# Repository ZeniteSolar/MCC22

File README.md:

# MCC22

## Build
```bash
cd firmware
make -j16 -f STM32Make.make
```

MPPT Battery charger

| Input Voltage     | 0 ~ 30 V  |
| ----------------: | :-------- |
|   Output Voltage  | 21 ~ 60V  |
| Output Power      | 300 W     |
| Efficiency        | > 90%     |

## 3D Model

## Soldered board

# Testing Guide for the MCC22 Board

Follow the steps below, if any value differs from the expected, abort the test. Power off and on after each step. Always limit the power source to 18V at 100mA. Use this [link](https://htmlpreview.github.io/?https://github.com/ZeniteSolar/MCC22/blob/main/hardware/main/bom/ibom.html) to find components on the board.

## Steps

1. Without any jumpers, connect the CAN with 18V, consumption should be approximately 1mA. On the power pin header (J601) there should be 5V and 3.3V at their respective pins.
2. Connect the STM 3.3V Enable jumper (JP101), consumption should be approximately 1mA.
3. Connect the STM32 Supply Enable jumper (JP201), consumption should be approximately 5mA. There should be 3.3V between the pins of capacitors C208 and C210.
4. Connect the STM 5V Enable jumper (JP103), consumption should be approximately 5mA. There should be 3V across the pins of capacitor C204.
5. Connect the Analog_Ref jumper (JP203) between the central pin and 3V_ref, consumption should be approximately 30mA. There should be 3V across the pins of capacitor C211.
6. Flash the STM32 (power should be on). When power is cycled, all LEDs should light up in sequence, excluding the Bat OverV LED. There should be a PWM signal on pin 1 of the PWM Enable jumper (JP106).
7. Connect the Enable_Analog jumper (JP102), the consumption should be approximately 5mA.
8. Connect a serial-USB converter and send the command `WRTE:SYST:PING?` to verify if UART is functioning, the response should be `PONG`.
9. Send the command `READ:MEAS:ALLM?`. After activating this flag, the board will continuously send the measurements it takes.
10. Connect a 10 Ohm resistor at the controller's output.
11. Send the command `WRTE:CTRL:ALGO:FIXD:0000.0000` to deactivate the PWM.
12. Connect the Disable_Vpanel jumper (JP301), the consumption should remain close to 5mA.
13. Connect the Disable_Vbat jumper (JP302), the consumption should remain close to 5mA.
14. Connect the Disable_Ibat jumper (JP304), the consumption should remain close to 5mA.
15. Connect the Disable_Ipanel jumper (JP303), the consumption should remain close to 5mA.
16. Connect a voltage source at P+ and P- with zero voltage and current at 10mA, increase the voltage to 30V and the VPan value on UART should follow the source voltage.
17. Connect a voltage source at B+ and B- with zero voltage and current at 10mA, increase the voltage to 60V and the Vbat value on UART should follow the source voltage.
18. Connect the Enable_Driver jumper (JP104) and consumption should be approximately 10mA. There should be 15V between pins 3 and 4 of the driver source (PS501).
19. Connect the Enable_Driver_5V jumper (JP502), Enable_Driver jumper (JP501), and Enable_PWM jumper (JP106), and the consumption should be approximately 12mA.
20. Send the command `WRTE:CTRL:ALGO:FIXD:0000.6000` to fix the PWM at 60%. Attach the oscilloscope's GND to test point S (TP404) **Other channels should have their GND disconnected!** and channel 1 to test point G0 (TP401). There should appear a square signal with a 60% duty cycle, same for G1 (TP402).
21. Connect a 10 Ohm load at the controller's output. Send the command `WRTE:CTRL:ALGO:FIXD:0000.6000`, connect a voltage source at P+ and P- with zero voltage and current at 1A, increase the voltage until the source limits and the Ipan value on UART should follow the source current.

Note: If any of the conditions are not met, there might be a potential issue with the board.

## Tests

All tests are in [this](./tests/tests.md) separated document.

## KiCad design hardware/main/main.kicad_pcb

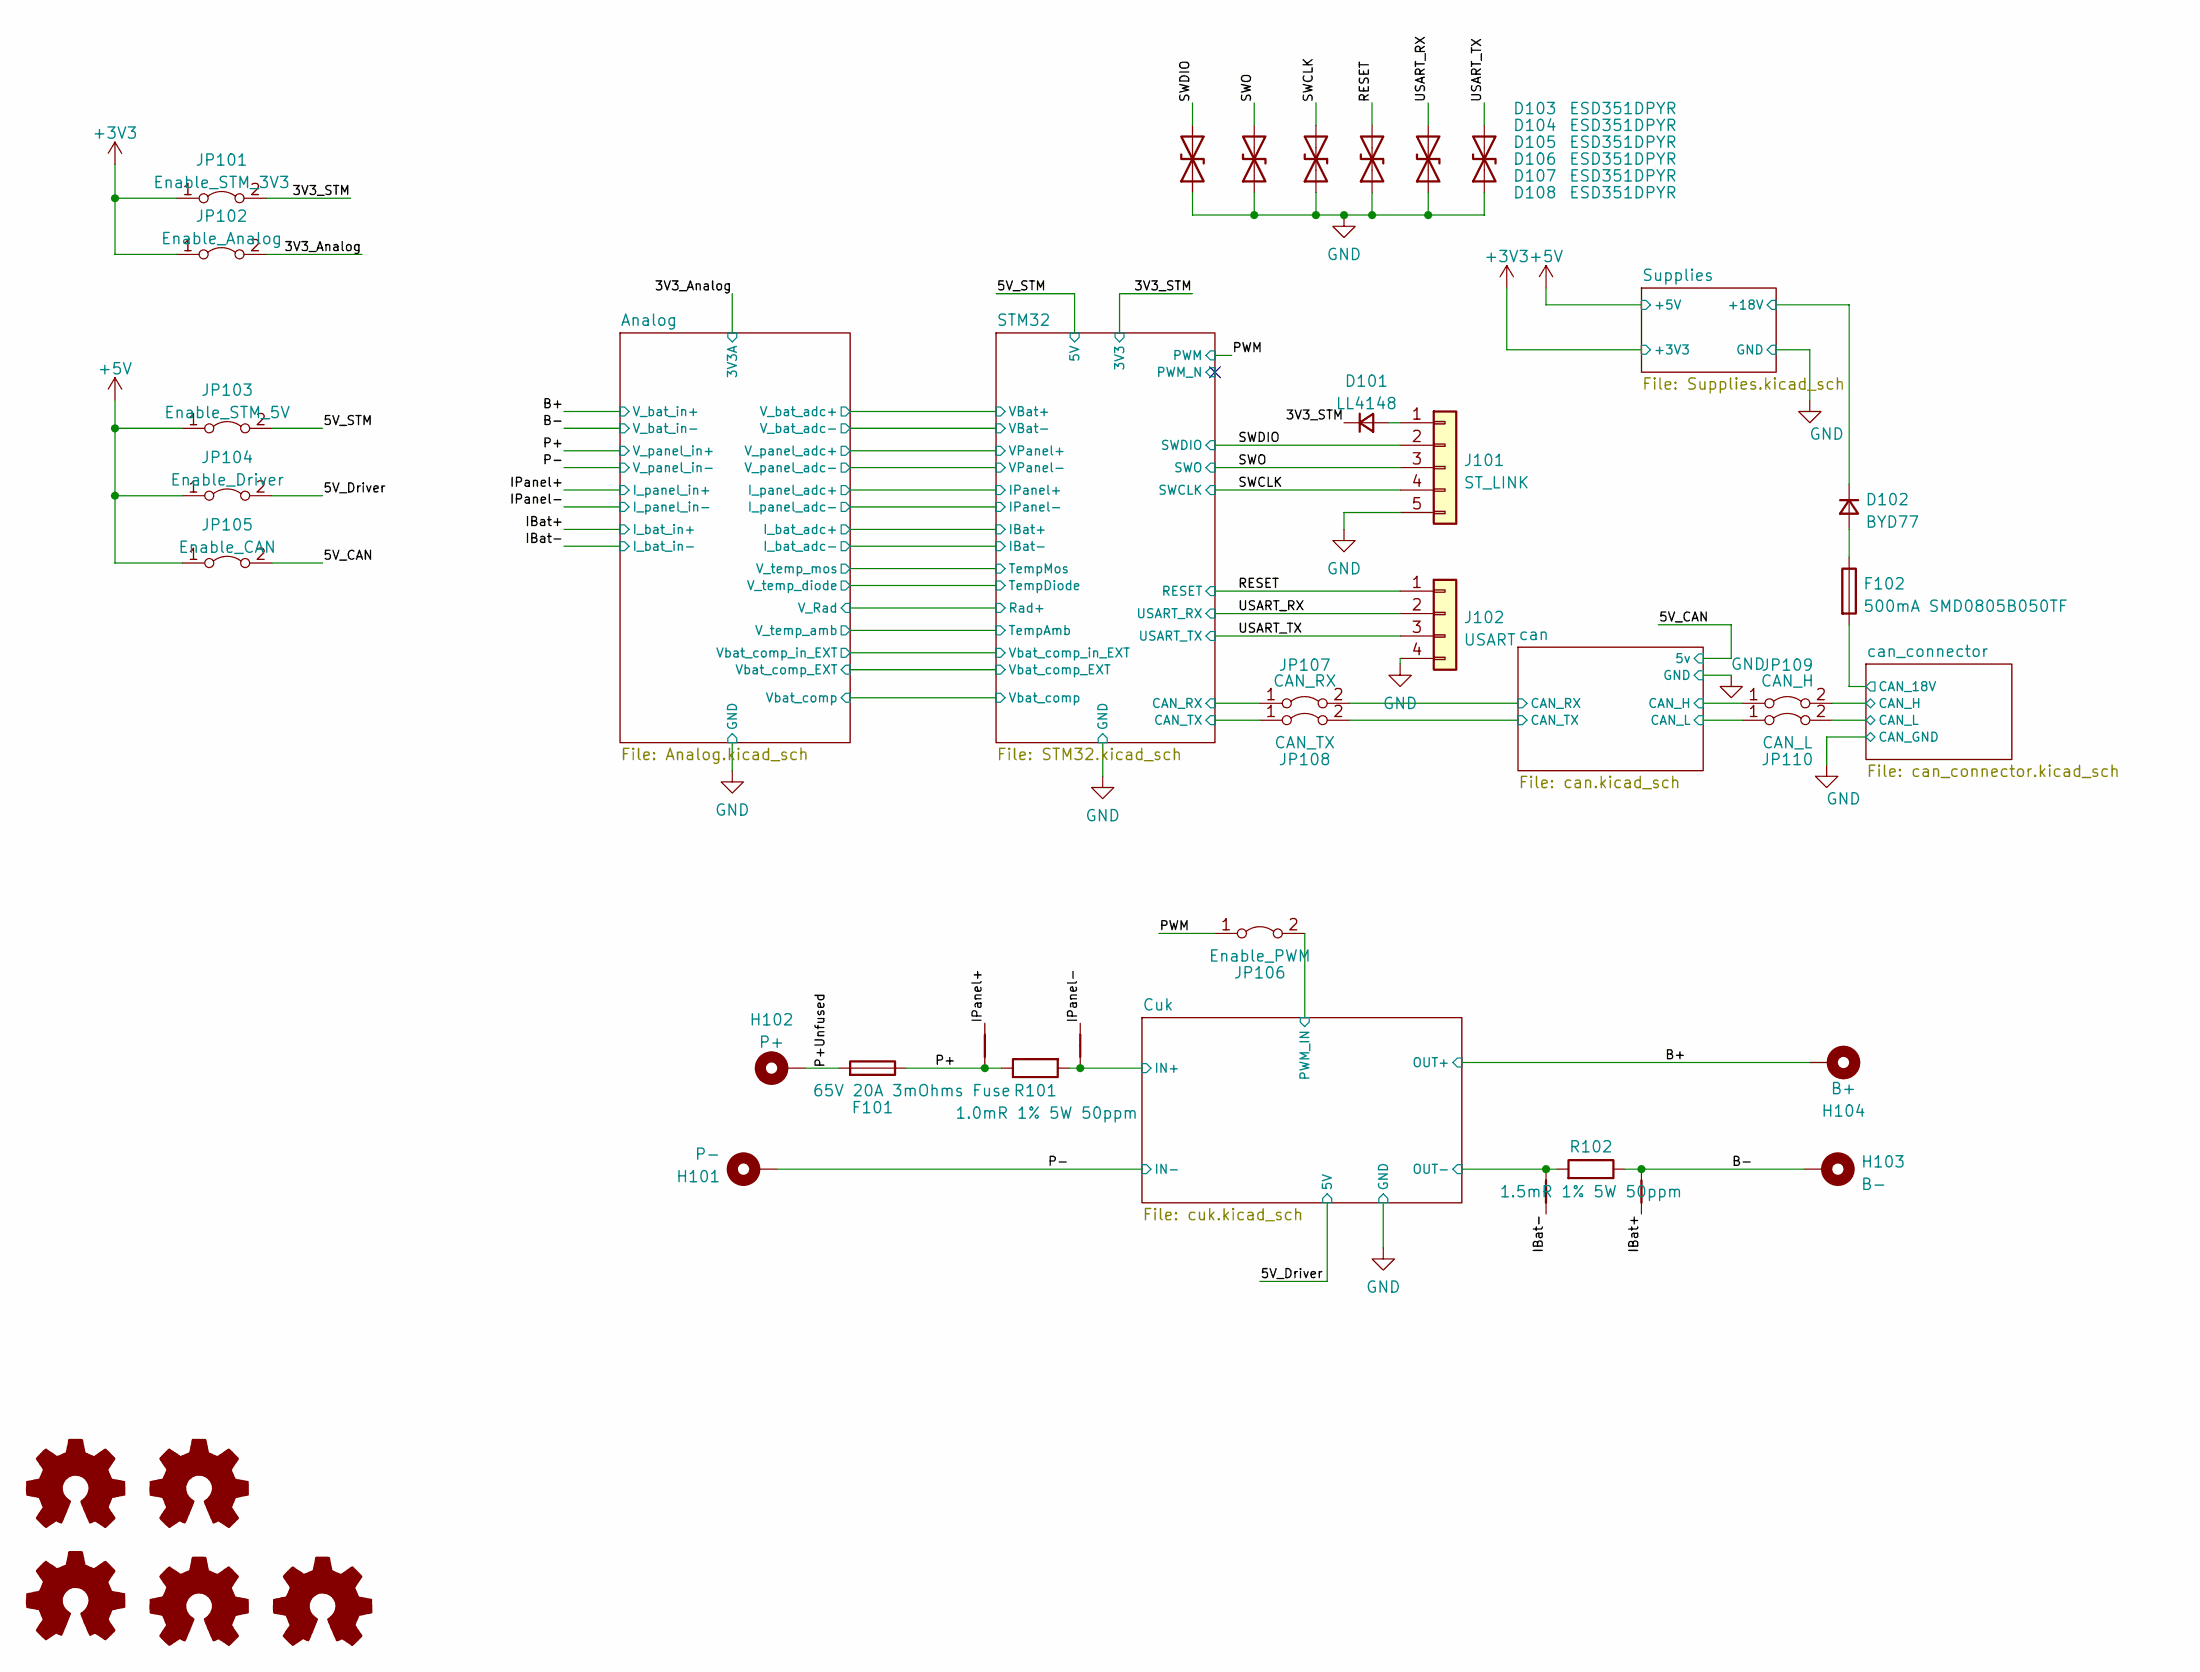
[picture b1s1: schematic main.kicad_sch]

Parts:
D101: LL4148; D_MiniMELF_Handsoldering
D102: BYD77; D_MiniMELF_Handsoldering
D103, D104, D105, D106, D107, D108: ESD351DPYR; D_0402_1005Metric_Pad0.77x0.64mm_HandSolder
F101: 65V 20A 3mOhms Fuse; S6125-F
F102: 500mA SMD0805B050TF; Fuse_0805_2012Metric_Pad1.15x1.40mm_HandSolder
H101: P-; MountingHole_13mmx13mm_Rectangular
H102: P+; MountingHole_13mmx13mm_Rectangular
H103: B-; MountingHole_13mmx13mm_Rectangular
H104: B+; MountingHole_13mmx13mm_Rectangular
J101: ST_LINK; PinSocket_1x05_P2.54mm_Horizontal_SMD
J102: USART; PinSocket_1x04_P2.54mm_Horizontal_SMD
JP101: Enable_STM_3V3; SolderJumper-2_P0.5mm_Open_TrianglePad0.8x0.5mm
JP102: Enable_Analog; SolderJumper-2_P0.5mm_Open_TrianglePad0.8x0.5mm
JP103: Enable_STM_5V; SolderJumper-2_P0.5mm_Open_TrianglePad0.8x0.5mm
JP104: Enable_Driver; SolderJumper-2_P0.5mm_Open_TrianglePad0.8x0.5mm
JP105: Enable_CAN; SolderJumper-2_P0.5mm_Open_TrianglePad0.8x0.5mm
JP106: Enable_PWM; SolderJumper-2_P0.5mm_Open_TrianglePad0.8x0.5mm
JP107: CAN_RX; SolderJumper-2_P0.5mm_Open_TrianglePad0.8x0.5mm
JP108: CAN_TX; SolderJumper-2_P0.5mm_Open_TrianglePad0.8x0.5mm
JP109: CAN_H; SolderJumper-2_P0.5mm_Open_TrianglePad0.8x0.5mm
JP110: CAN_L; SolderJumper-2_P0.5mm_Open_TrianglePad0.8x0.5mm
LOGO101: Logo_Open_Hardware_Small; symbol_logoZenite
LOGO102: Logo_Open_Hardware_Small; synbol_logoifsc
LOGO103: Logo_Open_Hardware_Small; OSHW-Logo_5.7x6mm_SilkScreen
LOGO104: Logo_Open_Hardware_Small; symbol_logoZenite_small
LOGO105: Logo_Open_Hardware_Small; synbol_logoifsc_small
NT101, NT102, NT104: NetTie_2; NetTie-2_SMD_Pad0.3mm
NT103: Resistor_SMD:R_0201_0603Metric; NetTie-2_SMD_Pad0.3mm
R101: 1.0mR 1% 5W 50ppm; R_2512_6332Metric_Pad1.40x3.35mm_HandSolder
R102: 1.5mR 1% 5W 50ppm; R_2512_6332Metric_Pad1.40x3.35mm_HandSolder

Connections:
+3V3: JP101.1 (A), JP102.1 (A); also elsewhere on the board
+5V: JP103.1 (A), JP104.1 (A), JP105.1 (A); also elsewhere on the board
/3V3_Analog: JP102.2 (B); also elsewhere on the board
/3V3_STM: D101.1 (K), JP101.2 (B); also elsewhere on the board
/5V_CAN: JP105.2 (B); also elsewhere on the board
/5V_Driver: JP104.2 (B); also elsewhere on the board
/5V_STM: JP103.2 (B); also elsewhere on the board
/B+: H104.1; also elsewhere on the board
/B-: H103.1, NT104.2, R102.1; also elsewhere on the board
/Cuk/A: NT102.2, NT103.2, R101.2, R102.2; also elsewhere on the board
/Cuk/PWM_IN: JP106.2 (B); also elsewhere on the board
/IBat+: NT104.1; also elsewhere on the board
/IBat-: NT103.1; also elsewhere on the board
/IPanel+: NT101.1; also elsewhere on the board
/IPanel-: NT102.1; also elsewhere on the board
/P+: F101.1, NT101.2, R101.1; also elsewhere on the board
/P+Unfused: F101.2, H102.1
/P-: H101.1; also elsewhere on the board
/PWM: JP106.1 (A); also elsewhere on the board
/RESET: D106.2 (A2), J102.1; also elsewhere on the board
/STM32/CAN_RX: JP107.1 (A); also elsewhere on the board
/STM32/CAN_TX: JP108.1 (A); also elsewhere on the board
/SWCLK: D105.2 (A2), J101.4; also elsewhere on the board
/SWDIO: D103.2 (A2), J101.2; also elsewhere on the board
/SWO: D104.2 (A2), J101.3; also elsewhere on the board
/Supplies/+18V: D102.1 (K); also elsewhere on the board
/USART_RX: D107.2 (A2), J102.2; also elsewhere on the board
/USART_TX: D108.2 (A2), J102.3; also elsewhere on the board
/can/CAN_H: JP109.1 (A); also elsewhere on the board
/can/CAN_L: JP110.1 (A); also elsewhere on the board
/can/CAN_RX: JP107.2 (B); also elsewhere on the board
/can/CAN_TX: JP108.2 (B); also elsewhere on the board
/can_connector/CAN_18V: F102.2; also elsewhere on the board
/can_connector/CAN_H: JP109.2 (B); also elsewhere on the board
/can_connector/CAN_L: JP110.2 (B); also elsewhere on the board
GND: D103.1 (A1), D104.1 (A1), D105.1 (A1), D106.1 (A1), D107.1 (A1), D108.1 (A1), J101.5, J102.4; also elsewhere on the board
unnamed: D101.2 (A), J101.1
unnamed: D102.2 (A), F102.1

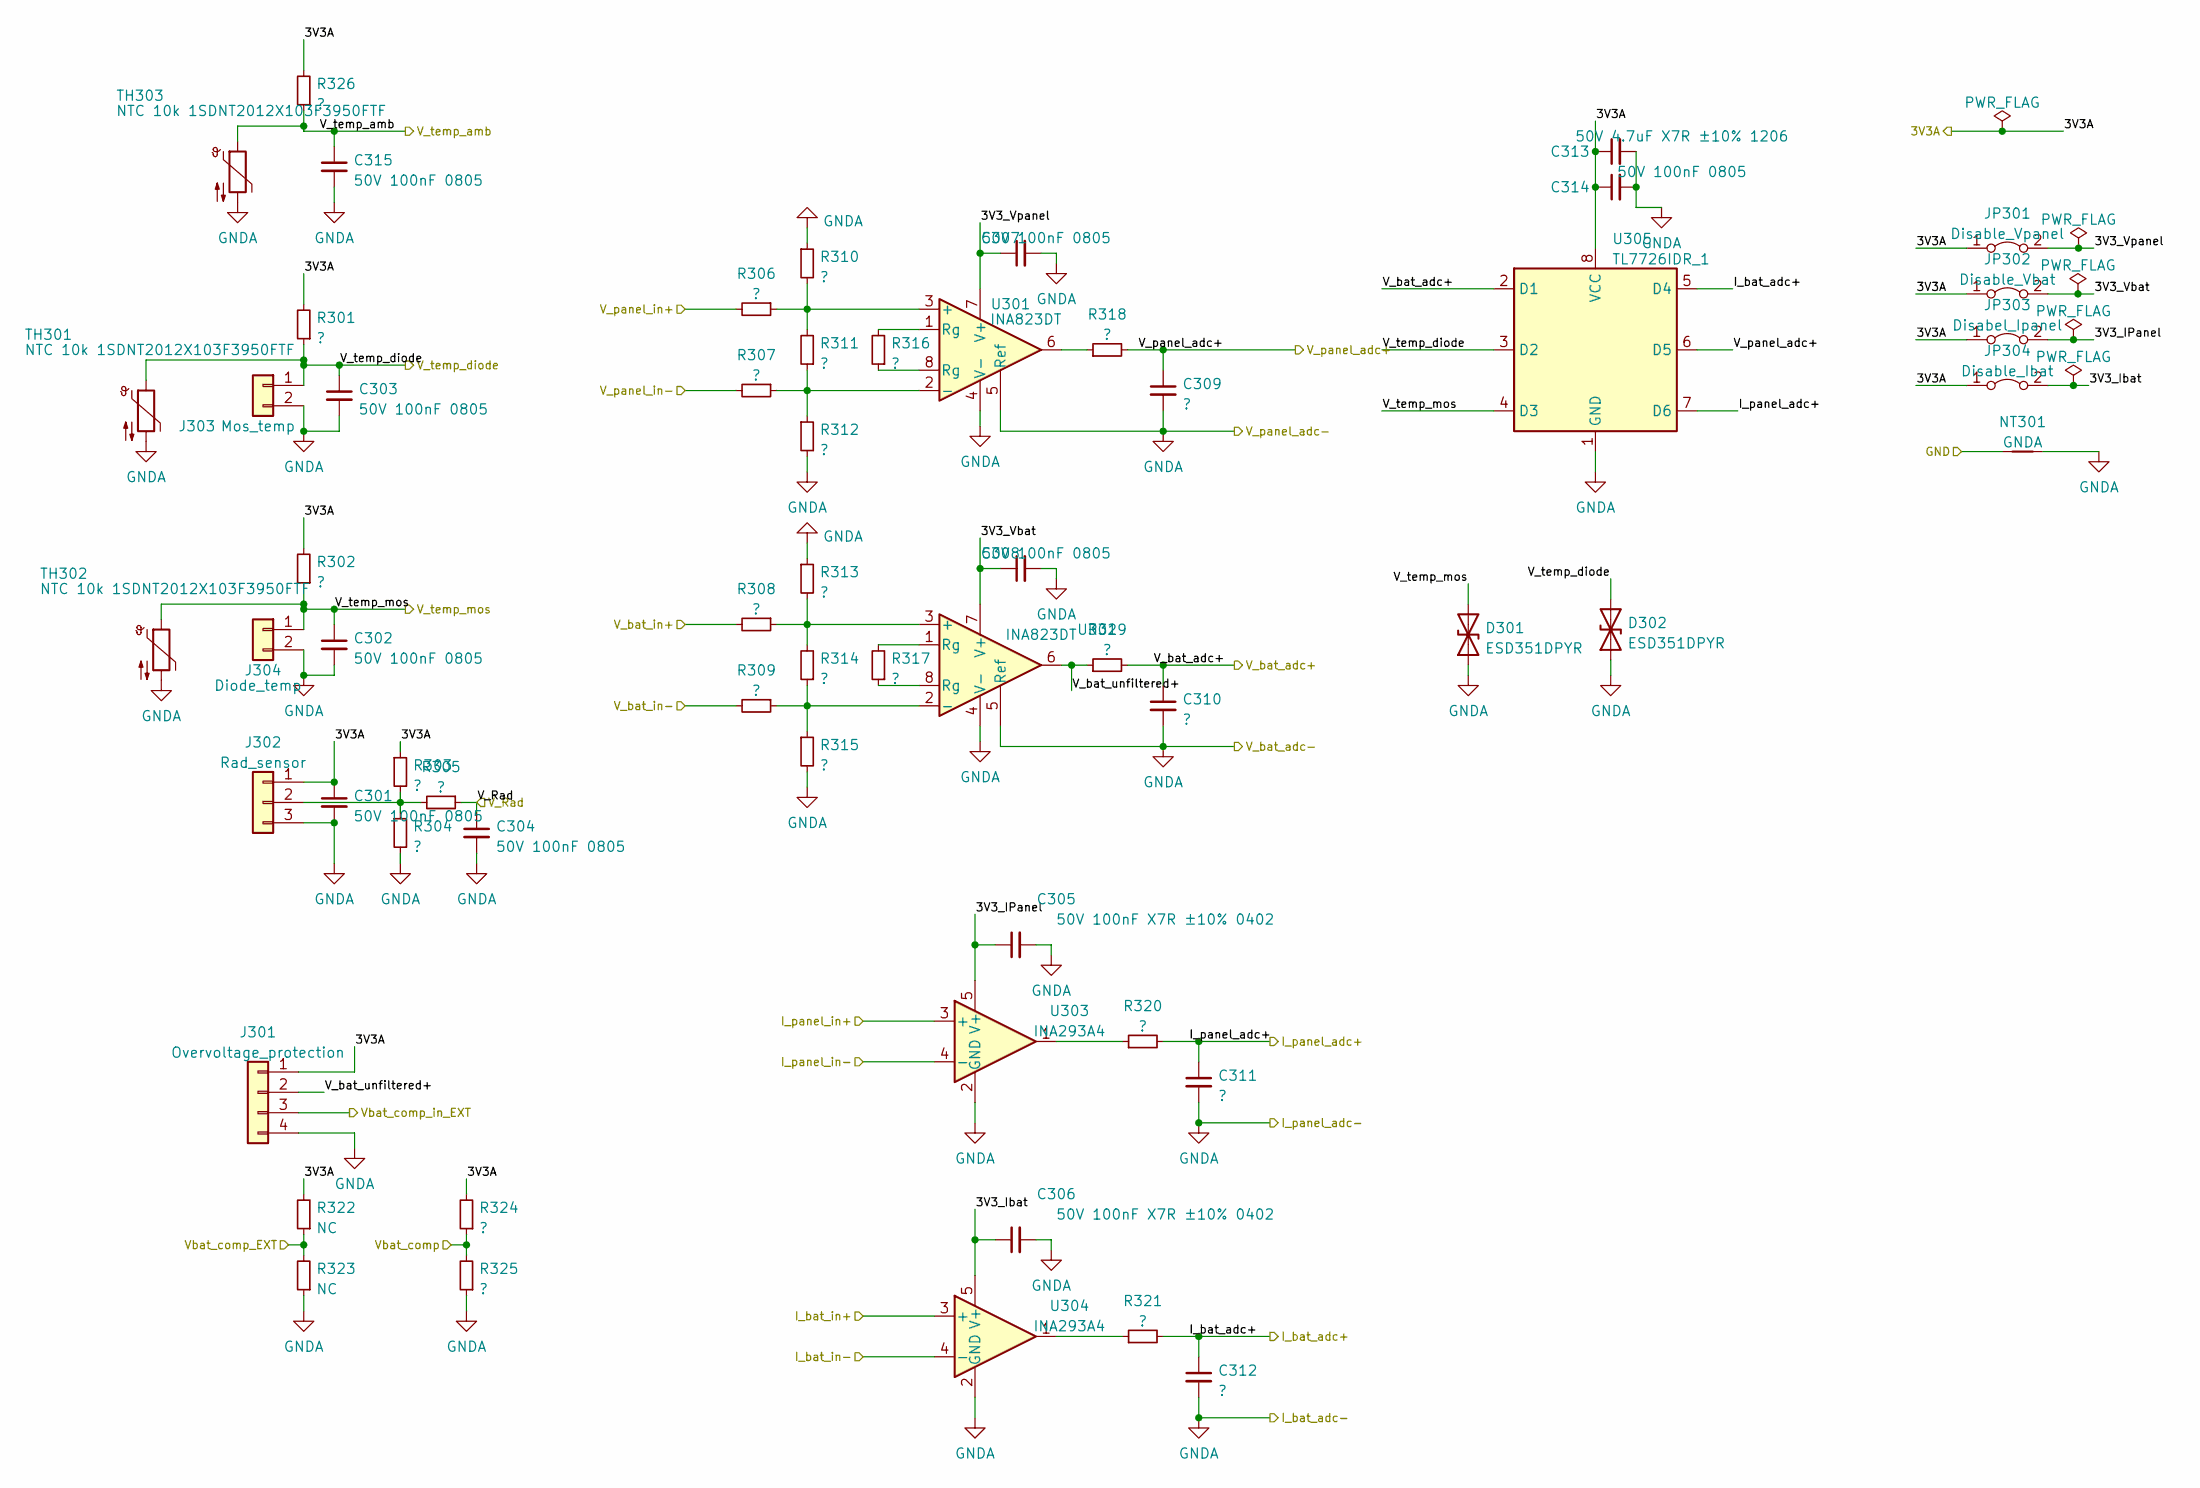
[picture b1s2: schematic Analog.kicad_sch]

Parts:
C301, C302, C303, C304, C307, C308, C314, C315: 50V 100nF 0805; C_0805_2012Metric_Pad1.18x1.45mm_HandSolder
C305, C306: 50V 100nF X7R ±10% 0402; C_0402_1005Metric_Pad0.74x0.62mm_HandSolder
C309, C310, C311, C312: ?; C_0805_2012Metric_Pad1.18x1.45mm_HandSolder
C313: 50V 4.7uF X7R ±10% 1206; C_1206_3216Metric_Pad1.33x1.80mm_HandSolder
D301, D302: ESD351DPYR; D_0402_1005Metric_Pad0.77x0.64mm_HandSolder
J301: Overvoltage_protection; PinHeader_1x04_P2.54mm_Vertical
J302: Rad_sensor; PinHeader_1x03_P2.54mm_Vertical
J303: Mos_temp; PinHeader_1x02_P2.54mm_Vertical
J304: Diode_temp; PinHeader_1x02_P2.54mm_Vertical
JP301: Disable_Vpanel; SolderJumper-2_P0.5mm_Open_TrianglePad0.8x0.5mm
JP302: Disable_Vbat; SolderJumper-2_P0.5mm_Open_TrianglePad0.8x0.5mm
JP303: Disabel_Ipanel; SolderJumper-2_P0.5mm_Open_TrianglePad0.8x0.5mm
JP304: Disable_Ibat; SolderJumper-2_P0.5mm_Open_TrianglePad0.8x0.5mm
NT301: GNDA; NetTie-2_SMD_Pad0.3mm
R301, R302, R303, R304, R305, R306, R307, R308, R309, R310, R311, R312, R313, R314, R315, R316, R317, R318, R319, R320, R321, R324, R325, R326: ?; R_0805_2012Metric_Pad1.20x1.40mm_HandSolder
R322, R323: NC; R_0805_2012Metric_Pad1.20x1.40mm_HandSolder
TH301, TH302, TH303: NTC 10k 1SDNT2012X103F3950FTF; R_0805_2012Metric_Pad1.20x1.40mm_HandSolder
U301, U302: INA823DT; SOIC-8_3.9x4.9mm_P1.27mm
U303, U304: INA293A4; SOT-23-5_HandSoldering
U305: TL7726IDR_1; SOIC-8_3.9x4.9mm_P1.27mm

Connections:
/3V3_Analog: C301.1, C313.1, C314.1, J301.1, J302.1, JP301.1 (A), JP302.1 (A), JP303.1 (A), JP304.1 (A), R301.2, R302.2, R303.1, R322.2, R324.2, R326.2, U305.8 (VCC); also elsewhere on the board
/Analog/3V3_IPanel: C305.1, JP303.2 (B), U303.5 (V+)
/Analog/3V3_Ibat: C306.1, JP304.2 (B), U304.5 (V+)
/Analog/3V3_Vbat: C308.1, JP302.2 (B), U302.7 (V+)
/Analog/3V3_Vpanel: C307.1, JP301.2 (B), U301.7 (V+)
/Analog/I_bat_adc+: C312.1, R321.2, U305.5 (D4); also elsewhere on the board
/Analog/I_panel_adc+: C311.1, R320.2, U305.7 (D6); also elsewhere on the board
/Analog/V_Rad: C304.1, R305.1; also elsewhere on the board
/Analog/V_bat_adc+: C310.1, R319.2, U305.2 (D1); also elsewhere on the board
/Analog/V_bat_unfiltered+: J301.2, R319.1, U302.6
/Analog/V_panel_adc+: C309.1, R318.2, U305.6 (D5); also elsewhere on the board
/Analog/V_temp_amb: C315.1, R326.1, TH303.1; also elsewhere on the board
/Analog/V_temp_diode: C303.1, D302.2 (A2), J303.1, R301.1, TH301.1, U305.3 (D2); also elsewhere on the board
/Analog/V_temp_mos: C302.1, D301.2 (A2), J304.1, R302.1, TH302.1, U305.4 (D3); also elsewhere on the board
/Analog/Vbat_comp: R324.1, R325.2; also elsewhere on the board
/Analog/Vbat_comp_EXT: R322.1, R323.2; also elsewhere on the board
/Analog/Vbat_comp_in_EXT: J301.3; also elsewhere on the board
/B+: R308.2; also elsewhere on the board
/B-: R309.2; also elsewhere on the board
/IBat+: U304.3 (+); also elsewhere on the board
/IBat-: U304.4 (-); also elsewhere on the board
/IPanel+: U303.3 (+); also elsewhere on the board
/IPanel-: U303.4 (-); also elsewhere on the board
/P+: R306.2; also elsewhere on the board
/P-: R307.2; also elsewhere on the board
GND: NT301.1; also elsewhere on the board
GNDA: C301.2, C302.2, C303.2, C304.2, C305.2, C306.2, C307.2, C308.2, C309.2, C310.2, C311.2, C312.2, C313.2, C314.2, C315.2, D301.1 (A1), D302.1 (A1), J301.4, J302.3, J303.2, J304.2, NT301.2, R304.2, R310.1, R312.2, R313.1, R315.2, R323.1, R325.1, TH301.2, TH302.2, TH303.2, U301.4 (V-), U301.5 (Ref), U302.4 (V-), U302.5 (Ref), U303.2 (GND), U304.2 (GND), U305.1 (GND); also elsewhere on the board
unnamed: J302.2, R303.2, R304.1, R305.2
unnamed: R306.1, R310.2, R311.2, U301.3 (+)
unnamed: R307.1, R311.1, R312.1, U301.2 (-)
unnamed: R308.1, R313.2, R314.2, U302.3 (+)
unnamed: R309.1, R314.1, R315.1, U302.2 (-)
unnamed: R316.1, U301.8 (Rg)
unnamed: R316.2, U301.1 (Rg)
unnamed: R317.1, U302.8 (Rg)
unnamed: R317.2, U302.1 (Rg)
unnamed: R318.1, U301.6
unnamed: R320.1, U303.1
unnamed: R321.1, U304.1

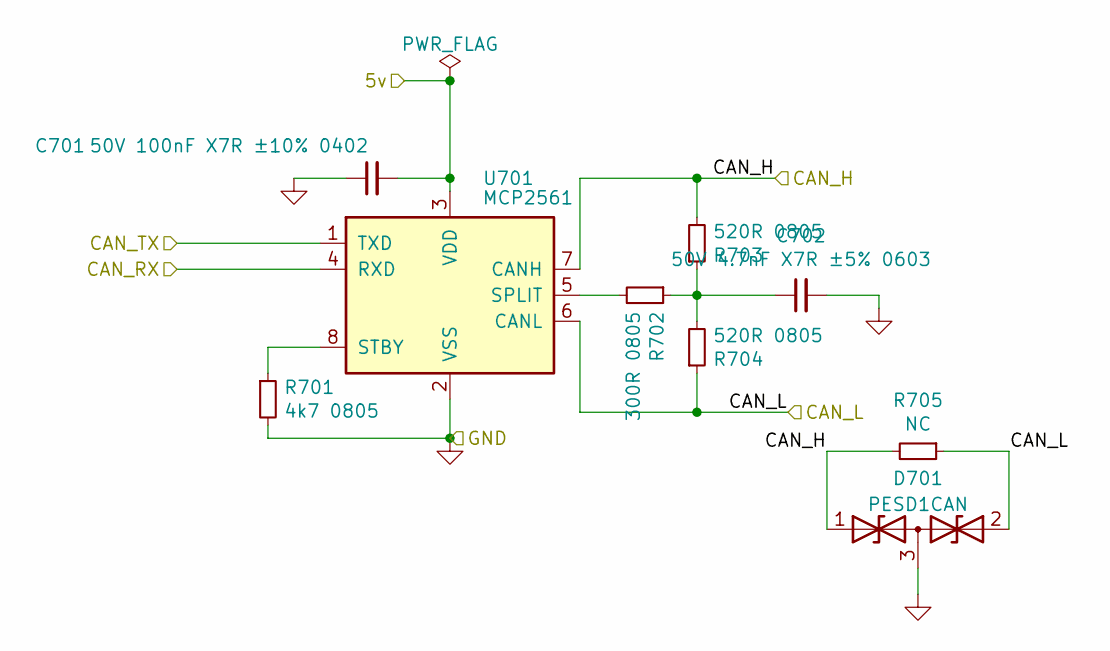
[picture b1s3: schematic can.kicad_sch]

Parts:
C701: 50V 100nF X7R ±10% 0402; C_0402_1005Metric_Pad0.74x0.62mm_HandSolder
C702: 50V 4.7nF X7R ±5% 0603; C_0603_1608Metric_Pad1.08x0.95mm_HandSolder
D701: PESD1CAN; SOT-23_Handsoldering
R701: 4k7 0805; R_0805_2012Metric_Pad1.20x1.40mm_HandSolder
R702: 300R 0805; R_0805_2012Metric_Pad1.20x1.40mm_HandSolder
R703, R704: 520R 0805; R_0805_2012Metric_Pad1.20x1.40mm_HandSolder
R705: NC; R_0805_2012Metric_Pad1.20x1.40mm_HandSolder
U701: MCP2561; SOIC-8_3.9x4.9mm_P1.27mm

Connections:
/5V_CAN: C701.2, U701.3 (VDD); also elsewhere on the board
/can/CAN_H: D701.1 (A1), R703.2, R705.2, U701.7 (CANH); also elsewhere on the board
/can/CAN_L: D701.2 (A2), R704.1, R705.1, U701.6 (CANL); also elsewhere on the board
/can/CAN_RX: U701.4 (RXD); also elsewhere on the board
/can/CAN_TX: U701.1 (TXD); also elsewhere on the board
GND: C701.1, C702.2, D701.3 (common), R701.2, U701.2 (VSS); also elsewhere on the board
unnamed: C702.1, R702.1, R703.1, R704.2
unnamed: R701.1, U701.8 (STBY)
unnamed: R702.2, U701.5 (SPLIT)

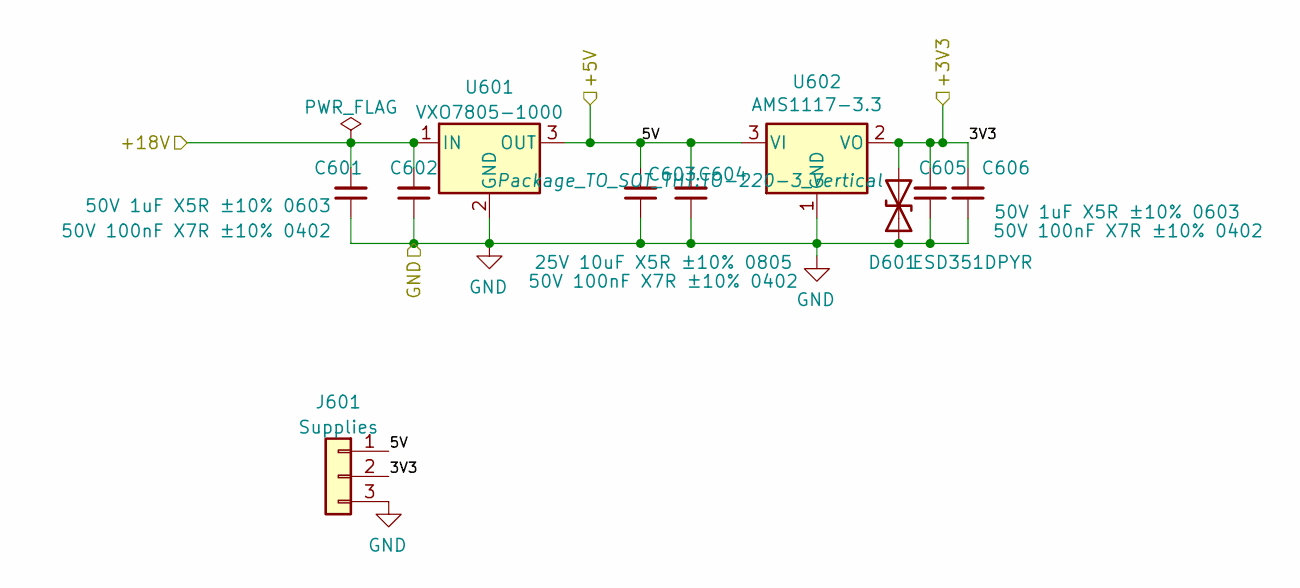
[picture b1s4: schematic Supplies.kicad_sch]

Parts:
C601, C606: 50V 1uF X5R ±10% 0603; C_1206_3216Metric_Pad1.33x1.80mm_HandSolder
C602, C604, C605: 50V 100nF X7R ±10% 0402; C_0603_1608Metric_Pad1.08x0.95mm_HandSolder
C603: 25V 10uF X5R ±10% 0805; C_1206_3216Metric_Pad1.33x1.80mm_HandSolder
D601: ESD351DPYR; D_0402_1005Metric_Pad0.77x0.64mm_HandSolder
J601: Supplies; PinHeader_1x03_P2.54mm_Vertical
U601: VXO7805-1000; TO-220-3_Vertical
U602: AMS1117-3.3; SOT-223-3_TabPin2

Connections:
+3V3: C605.2, C606.2, D601.2 (A2), J601.2, U602.2 (VO); also elsewhere on the board
+5V: C603.2, C604.2, J601.1, U601.3 (OUT), U602.3 (VI); also elsewhere on the board
/Supplies/+18V: C601.2, C602.2, U601.1 (IN); also elsewhere on the board
GND: C601.1, C602.1, C603.1, C604.1, C605.1, C606.1, D601.1 (A1), J601.3, U601.2 (GND), U602.1 (GND); also elsewhere on the board

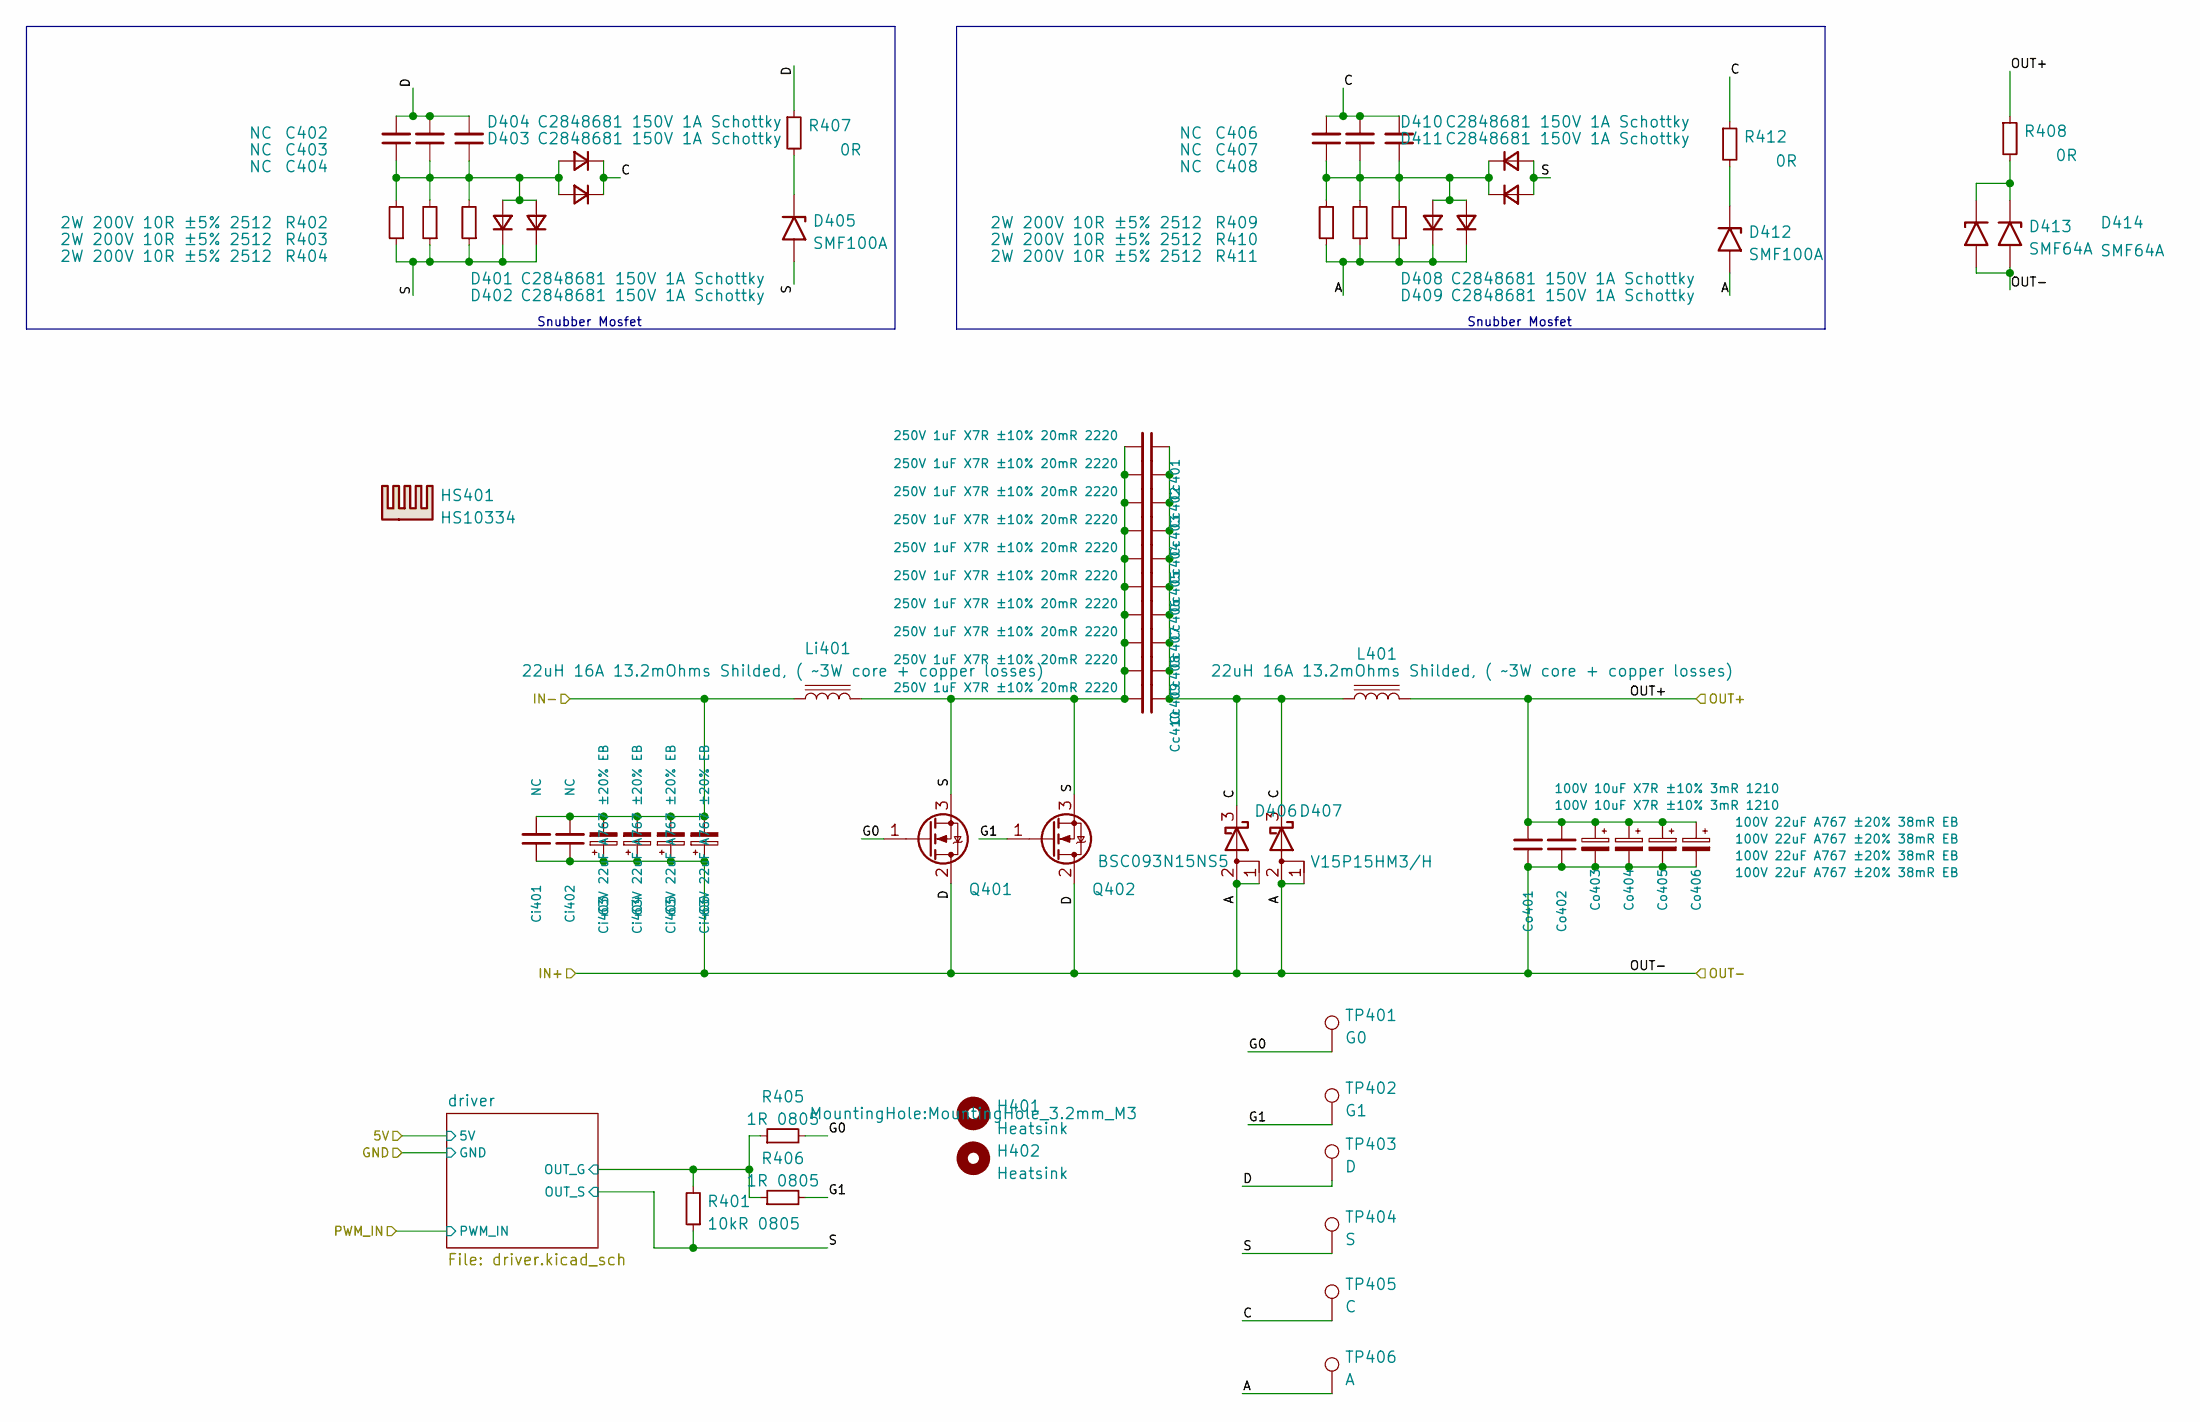
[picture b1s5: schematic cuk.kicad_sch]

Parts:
C402, C403, C404, C406, C407, C408: NC; C_1206_3216Metric_Pad1.33x1.80mm_HandSolder
Cc401, Cc402, Cc403, Cc404, Cc405, Cc406, Cc407, Cc408, Cc409, Cc410: 250V 1uF X7R ±10% 20mR 2220; C_2220_5650Metric
Ci401, Ci402: NC; C_1210_3225Metric
Ci403, Ci404, Ci405, Ci406: 63V 22uF A767 ±20% EB; CP_Elec_8x10
Co401, Co402: 100V 10uF X7R ±10% 3mR 1210; C_1210_3225Metric
Co403, Co404, Co405, Co406: 100V 22uF A767 ±20% 38mR EB; CP_Elec_10x12.5
D401, D402, D403, D404, D408, D409, D410, D411: C2848681 150V 1A Schottky; D_SMA
D405, D412: SMF100A; D_SOD-123F
D406, D407: V15P15HM3/H; TO-277A
D413, D414: SMF64A; D_SOD-123F
H401, H402: Heatsink; MountingHole_3.2mm_M3
HS401: HS10334; HS10334 60mmx17mm
L401: 22uH 16A 13.2mOhms Shilded, ( ~3W core + copper l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; L_Pulse_PM227
Li401: 22uH 16A 13.2mOhms Shilded, ( ~3W core + copper l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; L_Pulse_PM227
Q401, Q402: BSC093N15NS5; TDSON-8-3
R401: 10kR 0805; R_0805_2012Metric_Pad1.20x1.40mm_HandSolder
R402, R403, R404, R409, R410, R411: 2W 200V 10R ±5% 2512; R_2512_6332Metric_Pad1.40x3.35mm_HandSolder
R405, R406: 1R 0805; R_0805_2012Metric_Pad1.20x1.40mm_HandSolder
R407, R408, R412: 0R; R_0805_2012Metric_Pad1.20x1.40mm_HandSolder
TP401: G0; TestPoint_Pad_1.5x1.5mm
TP402: G1; TestPoint_Pad_1.5x1.5mm
TP403: D; TestPoint_Pad_1.5x1.5mm
TP404: S; TestPoint_Pad_1.5x1.5mm
TP405: C; TestPoint_Pad_1.5x1.5mm
TP406: A; TestPoint_Pad_1.5x1.5mm

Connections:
/B+: Co401.2, Co402.2, Co403.1, Co404.1, Co405.1, Co406.1, L401.2, R408.1; also elsewhere on the board
/Cuk/A: C402.2, C403.2, C404.2, Ci401.1, Ci402.1, Ci403.1, Ci404.1, Ci405.1, Ci406.1, Co401.1, Co402.1, Co403.2, Co404.2, Co405.2, Co406.2, D406.1 (A), D406.2 (A), D407.1 (A), D407.2 (A), D408.1 (K), D409.1 (K), D412.2 (A2), D413.2 (A2), D414.2 (A2), Q401.2 (D), Q402.2 (D), R407.1, R409.1, R410.1, R411.1, TP403.1, TP406.1; also elsewhere on the board
/Cuk/C: C406.2, C407.2, C408.2, Cc401.1, Cc402.1, Cc403.1, Cc404.1, Cc405.1, Cc406.1, Cc407.1, Cc408.1, Cc409.1, Cc410.1, D403.1 (K), D404.1 (K), D406.3 (K), D407.3 (K), L401.1, R412.1, TP405.1
/Cuk/G0: Q401.1 (G), R405.2, TP401.1
/Cuk/G1: Q402.1 (G), R406.2, TP402.1
/Cuk/S: Cc401.2, Cc402.2, Cc403.2, Cc404.2, Cc405.2, Cc406.2, Cc407.2, Cc408.2, Cc409.2, Cc410.2, D401.1 (K), D402.1 (K), D405.2 (A2), D410.2 (A), D411.2 (A), Li401.1, Q401.3 (S), Q402.3 (S), R401.1, R402.1, R403.1, R404.1, TP404.1; also elsewhere on the board
/Cuk/driver/OUT_G: R401.2, R405.1, R406.1; also elsewhere on the board
/P-: Ci401.2, Ci402.2, Ci403.2, Ci404.2, Ci405.2, Ci406.2, Li401.2; also elsewhere on the board
unnamed: C402.1, C403.1, C404.1, D401.2 (A), D402.2 (A), D403.2 (A), D404.2 (A), R402.2, R403.2, R404.2
unnamed: C406.1, C407.1, C408.1, D408.2 (A), D409.2 (A), D410.1 (K), D411.1 (K), R409.2, R410.2, R411.2
unnamed: D405.1 (A1), R407.2
unnamed: D412.1 (A1), R412.2
unnamed: D413.1 (A1), D414.1 (A1), R408.2

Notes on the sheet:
Snubber Mosfet

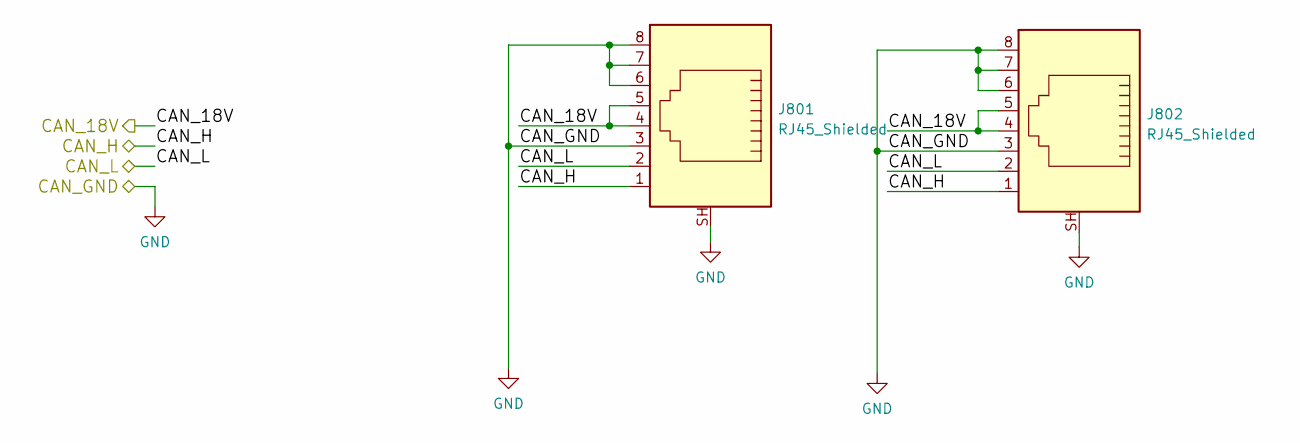
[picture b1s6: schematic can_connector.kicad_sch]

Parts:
J801, J802: RJ45_Shielded; RJ45_YH59_01

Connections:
/can_connector/CAN_18V: J801.4, J801.5, J802.4, J802.5; also elsewhere on the board
/can_connector/CAN_H: J801.1, J802.1; also elsewhere on the board
/can_connector/CAN_L: J801.2, J802.2; also elsewhere on the board
GND: J801.3, J801.6, J801.7, J801.8, J801.SH, J802.3, J802.6, J802.7, J802.8, J802.SH; also elsewhere on the board
